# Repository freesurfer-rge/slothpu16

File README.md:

# slothpu16

This is a major revision of [an earlier project](http://www.github.com/freesurfer-rge/slothpu/) to build a computer from 7400-series logic.
This implements a simple 16-bit CPU with a load/store architecture.

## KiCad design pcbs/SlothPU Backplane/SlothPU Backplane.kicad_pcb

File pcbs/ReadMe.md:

# SlothPU16 PCBs

This directory contains the KiCAD files which constitute SlothPU16.
They do rely on [my KiCAD components library](https://github.com/freesurfer-rge/kicad-components), and [one board](https://github.com/freesurfer-rge/slothpu/tree/main/pcbs/Tester) from the original SlothPU.

## General Description

SlothPU16 consists of five modules connected via a backplane:

- The Arithmetic Logic Unit (ALU)
- The Register File
- The Instruction Register
- The Program Counter
- The Pi Backplane Connector

The modules connect to the backplane (and backplane units connect to each other) with a common bus made from two 2x20 pin headers.
With the exception of the Pi Backplane Connector, each of these modules consists of a *carrier* board, which accepts daughter boards via 44-contact edge connectors.
For testing the daughter boards, *connector* PCBs are provided, which allow each to be tested via the [tester board from the original SlothPU](https://github.com/freesurfer-rge/slothpu/tree/main/pcbs/Tester).
While these connector boards also have twin 2x20 pin headers, these **do not** correspond to the Common Bus, and can **only** be used with the Tester board.
The carrier boards which constitute an entire functional module can also be tested in isolation by use of the Pi Backplane connector.

## The Common Bus

The common bus consists of two 2x20 pin headers, offering a total of 80 potential connections.
Not all of the pins are used, but the bus carries:

- The 16-bit A, B and C operand buses
- The 16-bit instruction bus
- Clock and Reset lines
- Signal lines for the individual clock cycles (Instruction Read, Instruction Store, Decode/Execute, Commit, PC Update)

## The Arithmetic Logic Unit

The ALU consists of its [carrier board](./ALU%20Carrier/) and the following daughter cards:

- [Barrel shifter](./Barrel%20Shifter/)
- [NAND/XOR](./NAND%20XOR/)
- [Comparator](./Comparator/)
- [Adder/Subtractor](./Adder%20Subtractor/)

With the exception of the comparator, two of each of these cards are required.
For testing purposes, the barrel shifter has its [own connector](./Barrel%20Shifter%20Connector/), while the other three share a [common connector](./ALU%20Test%20Connector/).
Note that *only one* of the daughter cards should plugged into the common ALU test connector at a time - no effort is made to prevent outputs from different daughter cards being connected.
Remember that **neither connector** uses the common bus.

## The Register File

The [Register File Carrier](./Register%20File%20Carrier/) accepts four identical copies of the [Register File](./Register%20File/).
Each Register file contains eight 8-bit registers, with one write port (from the C bus) and two read ports (the A & B buses).
A [connector](./Register%20File%20Connector/) allows the individual Register Files to be tested (remember that the connector board does **not** use the common bus).

## The Instruction Register

The [Instruction Register](./Instruction%20Register/) accepts a single daughter card, the 16-bit [Register with Reset](./Register%20with%20Reset/).
In addition to containing the instruction register itself, this module implements the 'SET' instruction.
This Register is supposed to be set to zero when power is connected, but for some reason it doesn't.
However, the Reset line does work correctly.
A [connector](./RwR%20Connector/) is provided for testing the register itself (remember that the connector board does **not** use the common bus).

## Program Counter

The [Program Counter](./Program%20Counter/) has two daughter cards - a second Register With Reset (which is the PC register) and an [incrementer](./Incrementer/).
The latter takes care of incrementing the program counter by two (unless a branch is taken), and has its own [test connector board](./Incrementer%20Connector/) (remember that the connector board does **not** use the common bus).

## Pi Backplane Connector

As the name suggests, [this board](./SlothPU%20Backplane/) connects a the standard 2x20 Raspberry Pi header to the Common Bus.
To this end, twin banks of input and output shift registers are used.
The output shift registers can have their outputs set to high impedance for when a connected module wishes to write to a bus.
However, the resolution of this impedance switch is at the bus level, not individual lines.

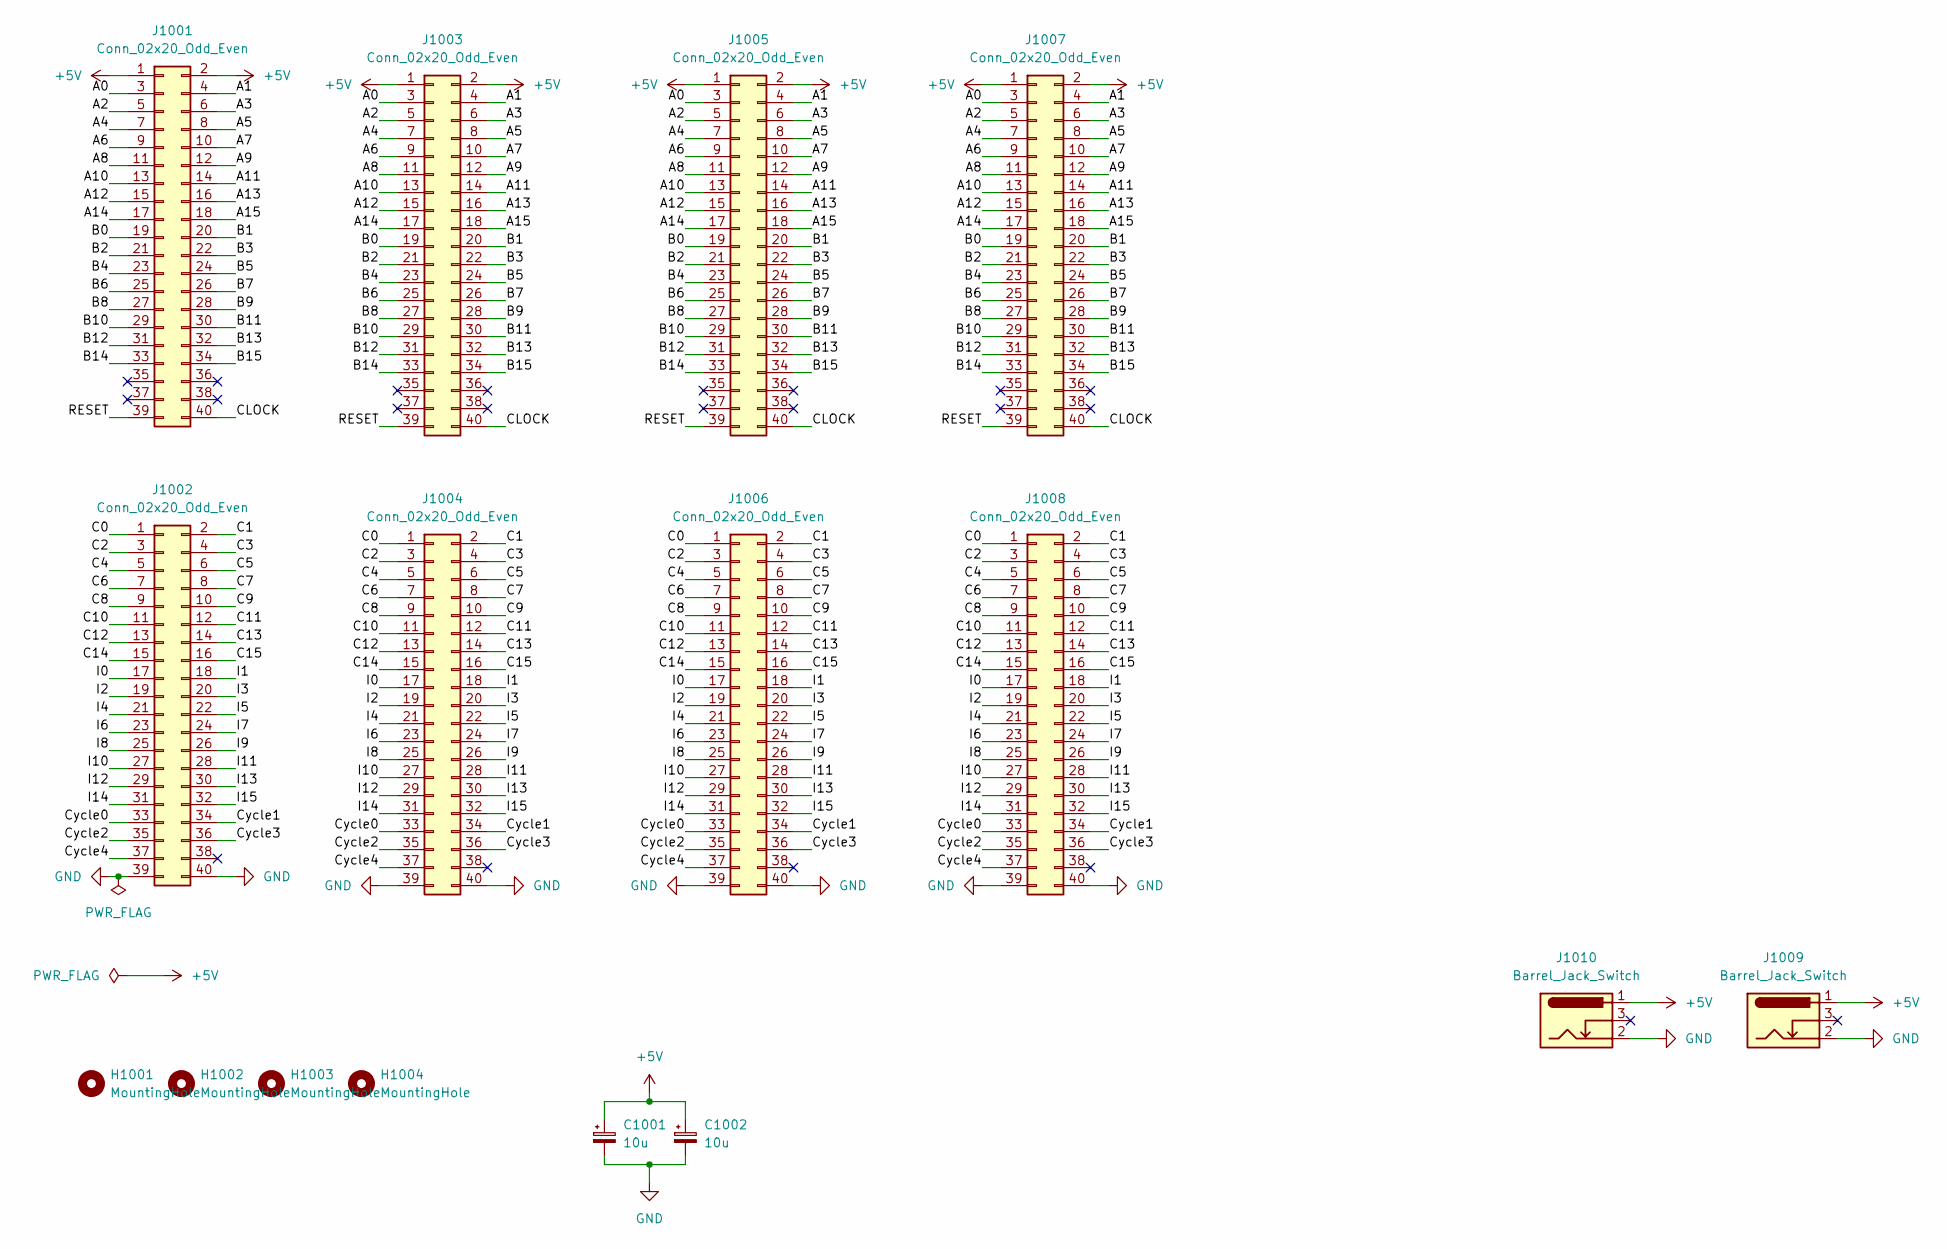
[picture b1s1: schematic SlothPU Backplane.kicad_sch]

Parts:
C1001, C1002: 10u; CP_Radial_D4.0mm_P1.50mm
H1001, H1002, H1003, H1004: MountingHole; MountingHole_2.7mm_M2.5_ISO7380
J1001, J1002, J1003, J1004, J1005, J1006, J1007, J1008: Conn_02x20_Odd_Even; PinHeader_2x20_P2.54mm_Vertical
J1009, J1010: Barrel_Jack_Switch; BarrelJack_Horizontal

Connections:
+5V: C1001.1, C1002.1, J1001.1, J1001.2, J1003.1, J1003.2, J1005.1, J1005.2, J1007.1, J1007.2, J1009.1, J1010.1
/A0: J1001.3, J1003.3, J1005.3, J1007.3
/A1: J1001.4, J1003.4, J1005.4, J1007.4
/A2: J1001.5, J1003.5, J1005.5, J1007.5
/A3: J1001.6, J1003.6, J1005.6, J1007.6
/A4: J1001.7, J1003.7, J1005.7, J1007.7
/A5: J1001.8, J1003.8, J1005.8, J1007.8
/A6: J1001.9, J1003.9, J1005.9, J1007.9
/A7: J1001.10, J1003.10, J1005.10, J1007.10
/A8: J1001.11, J1003.11, J1005.11, J1007.11
/A9: J1001.12, J1003.12, J1005.12, J1007.12
/A10: J1001.13, J1003.13, J1005.13, J1007.13
/A11: J1001.14, J1003.14, J1005.14, J1007.14
/A12: J1001.15, J1003.15, J1005.15, J1007.15
/A13: J1001.16, J1003.16, J1005.16, J1007.16
/A14: J1001.17, J1003.17, J1005.17, J1007.17
/A15: J1001.18, J1003.18, J1005.18, J1007.18
/B0: J1001.19, J1003.19, J1005.19, J1007.19
/B1: J1001.20, J1003.20, J1005.20, J1007.20
/B2: J1001.21, J1003.21, J1005.21, J1007.21
/B3: J1001.22, J1003.22, J1005.22, J1007.22
/B4: J1001.23, J1003.23, J1005.23, J1007.23
/B5: J1001.24, J1003.24, J1005.24, J1007.24
/B6: J1001.25, J1003.25, J1005.25, J1007.25
/B7: J1001.26, J1003.26, J1005.26, J1007.26
/B8: J1001.27, J1003.27, J1005.27, J1007.27
/B9: J1001.28, J1003.28, J1005.28, J1007.28
/B10: J1001.29, J1003.29, J1005.29, J1007.29
/B11: J1001.30, J1003.30, J1005.30, J1007.30
/B12: J1001.31, J1003.31, J1005.31, J1007.31
/B13: J1001.32, J1003.32, J1005.32, J1007.32
/B14: J1001.33, J1003.33, J1005.33, J1007.33
/B15: J1001.34, J1003.34, J1005.34, J1007.34
/C0: J1002.1, J1004.1, J1006.1, J1008.1
/C1: J1002.2, J1004.2, J1006.2, J1008.2
/C2: J1002.3, J1004.3, J1006.3, J1008.3
/C3: J1002.4, J1004.4, J1006.4, J1008.4
/C4: J1002.5, J1004.5, J1006.5, J1008.5
/C5: J1002.6, J1004.6, J1006.6, J1008.6
/C6: J1002.7, J1004.7, J1006.7, J1008.7
/C7: J1002.8, J1004.8, J1006.8, J1008.8
/C8: J1002.9, J1004.9, J1006.9, J1008.9
/C9: J1002.10, J1004.10, J1006.10, J1008.10
/C10: J1002.11, J1004.11, J1006.11, J1008.11
/C11: J1002.12, J1004.12, J1006.12, J1008.12
/C12: J1002.13, J1004.13, J1006.13, J1008.13
/C13: J1002.14, J1004.14, J1006.14, J1008.14
/C14: J1002.15, J1004.15, J1006.15, J1008.15
/C15: J1002.16, J1004.16, J1006.16, J1008.16
/CLOCK: J1001.40, J1003.40, J1005.40, J1007.40
/Cycle0: J1002.33, J1004.33, J1006.33, J1008.33
/Cycle1: J1002.34, J1004.34, J1006.34, J1008.34
/Cycle2: J1002.35, J1004.35, J1006.35, J1008.35
/Cycle3: J1002.36, J1004.36, J1006.36, J1008.36
/Cycle4: J1002.37, J1004.37, J1006.37, J1008.37
/I0: J1002.17, J1004.17, J1006.17, J1008.17
/I1: J1002.18, J1004.18, J1006.18, J1008.18
/I2: J1002.19, J1004.19, J1006.19, J1008.19
/I3: J1002.20, J1004.20, J1006.20, J1008.20
/I4: J1002.21, J1004.21, J1006.21, J1008.21
/I5: J1002.22, J1004.22, J1006.22, J1008.22
/I6: J1002.23, J1004.23, J1006.23, J1008.23
/I7: J1002.24, J1004.24, J1006.24, J1008.24
/I8: J1002.25, J1004.25, J1006.25, J1008.25
/I9: J1002.26, J1004.26, J1006.26, J1008.26
/I10: J1002.27, J1004.27, J1006.27, J1008.27
/I11: J1002.28, J1004.28, J1006.28, J1008.28
/I12: J1002.29, J1004.29, J1006.29, J1008.29
/I13: J1002.30, J1004.30, J1006.30, J1008.30
/I14: J1002.31, J1004.31, J1006.31, J1008.31
/I15: J1002.32, J1004.32, J1006.32, J1008.32
/RESET: J1001.39, J1003.39, J1005.39, J1007.39
GND: C1001.2, C1002.2, J1002.39, J1002.40, J1004.39, J1004.40, J1006.39, J1006.40, J1008.39, J1008.40, J1009.2, J1010.2

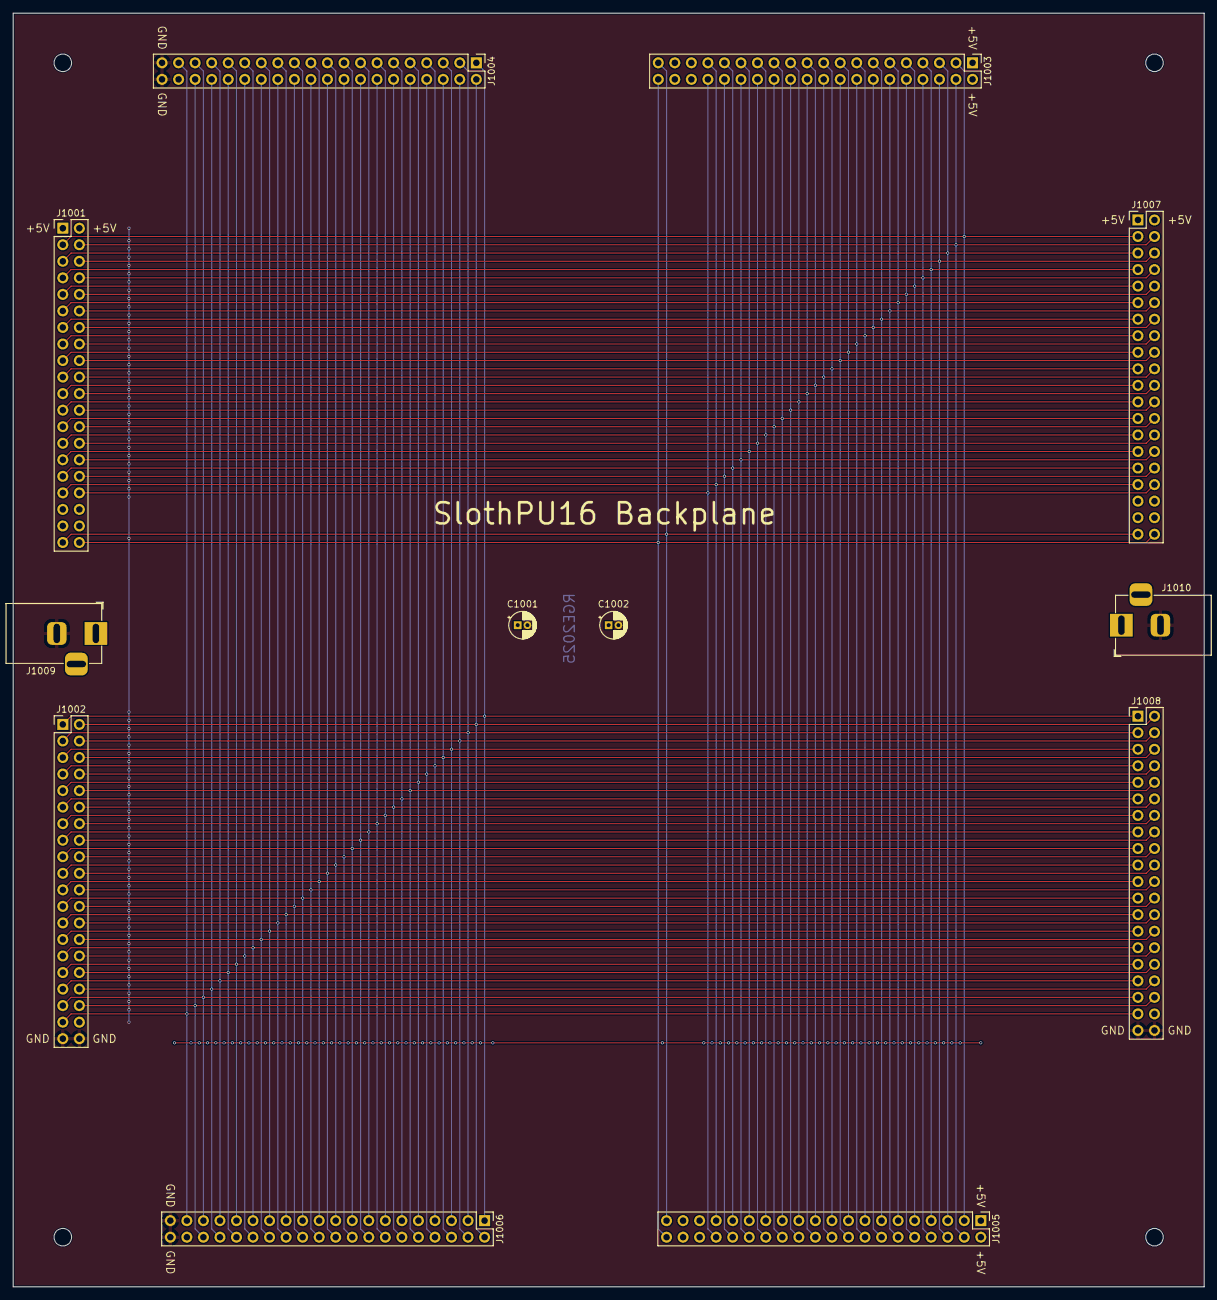
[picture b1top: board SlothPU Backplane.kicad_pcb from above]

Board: 2 copper layers, 182.9 x 195.6 mm, 16 parts (0 on the bottom side), 73 nets.

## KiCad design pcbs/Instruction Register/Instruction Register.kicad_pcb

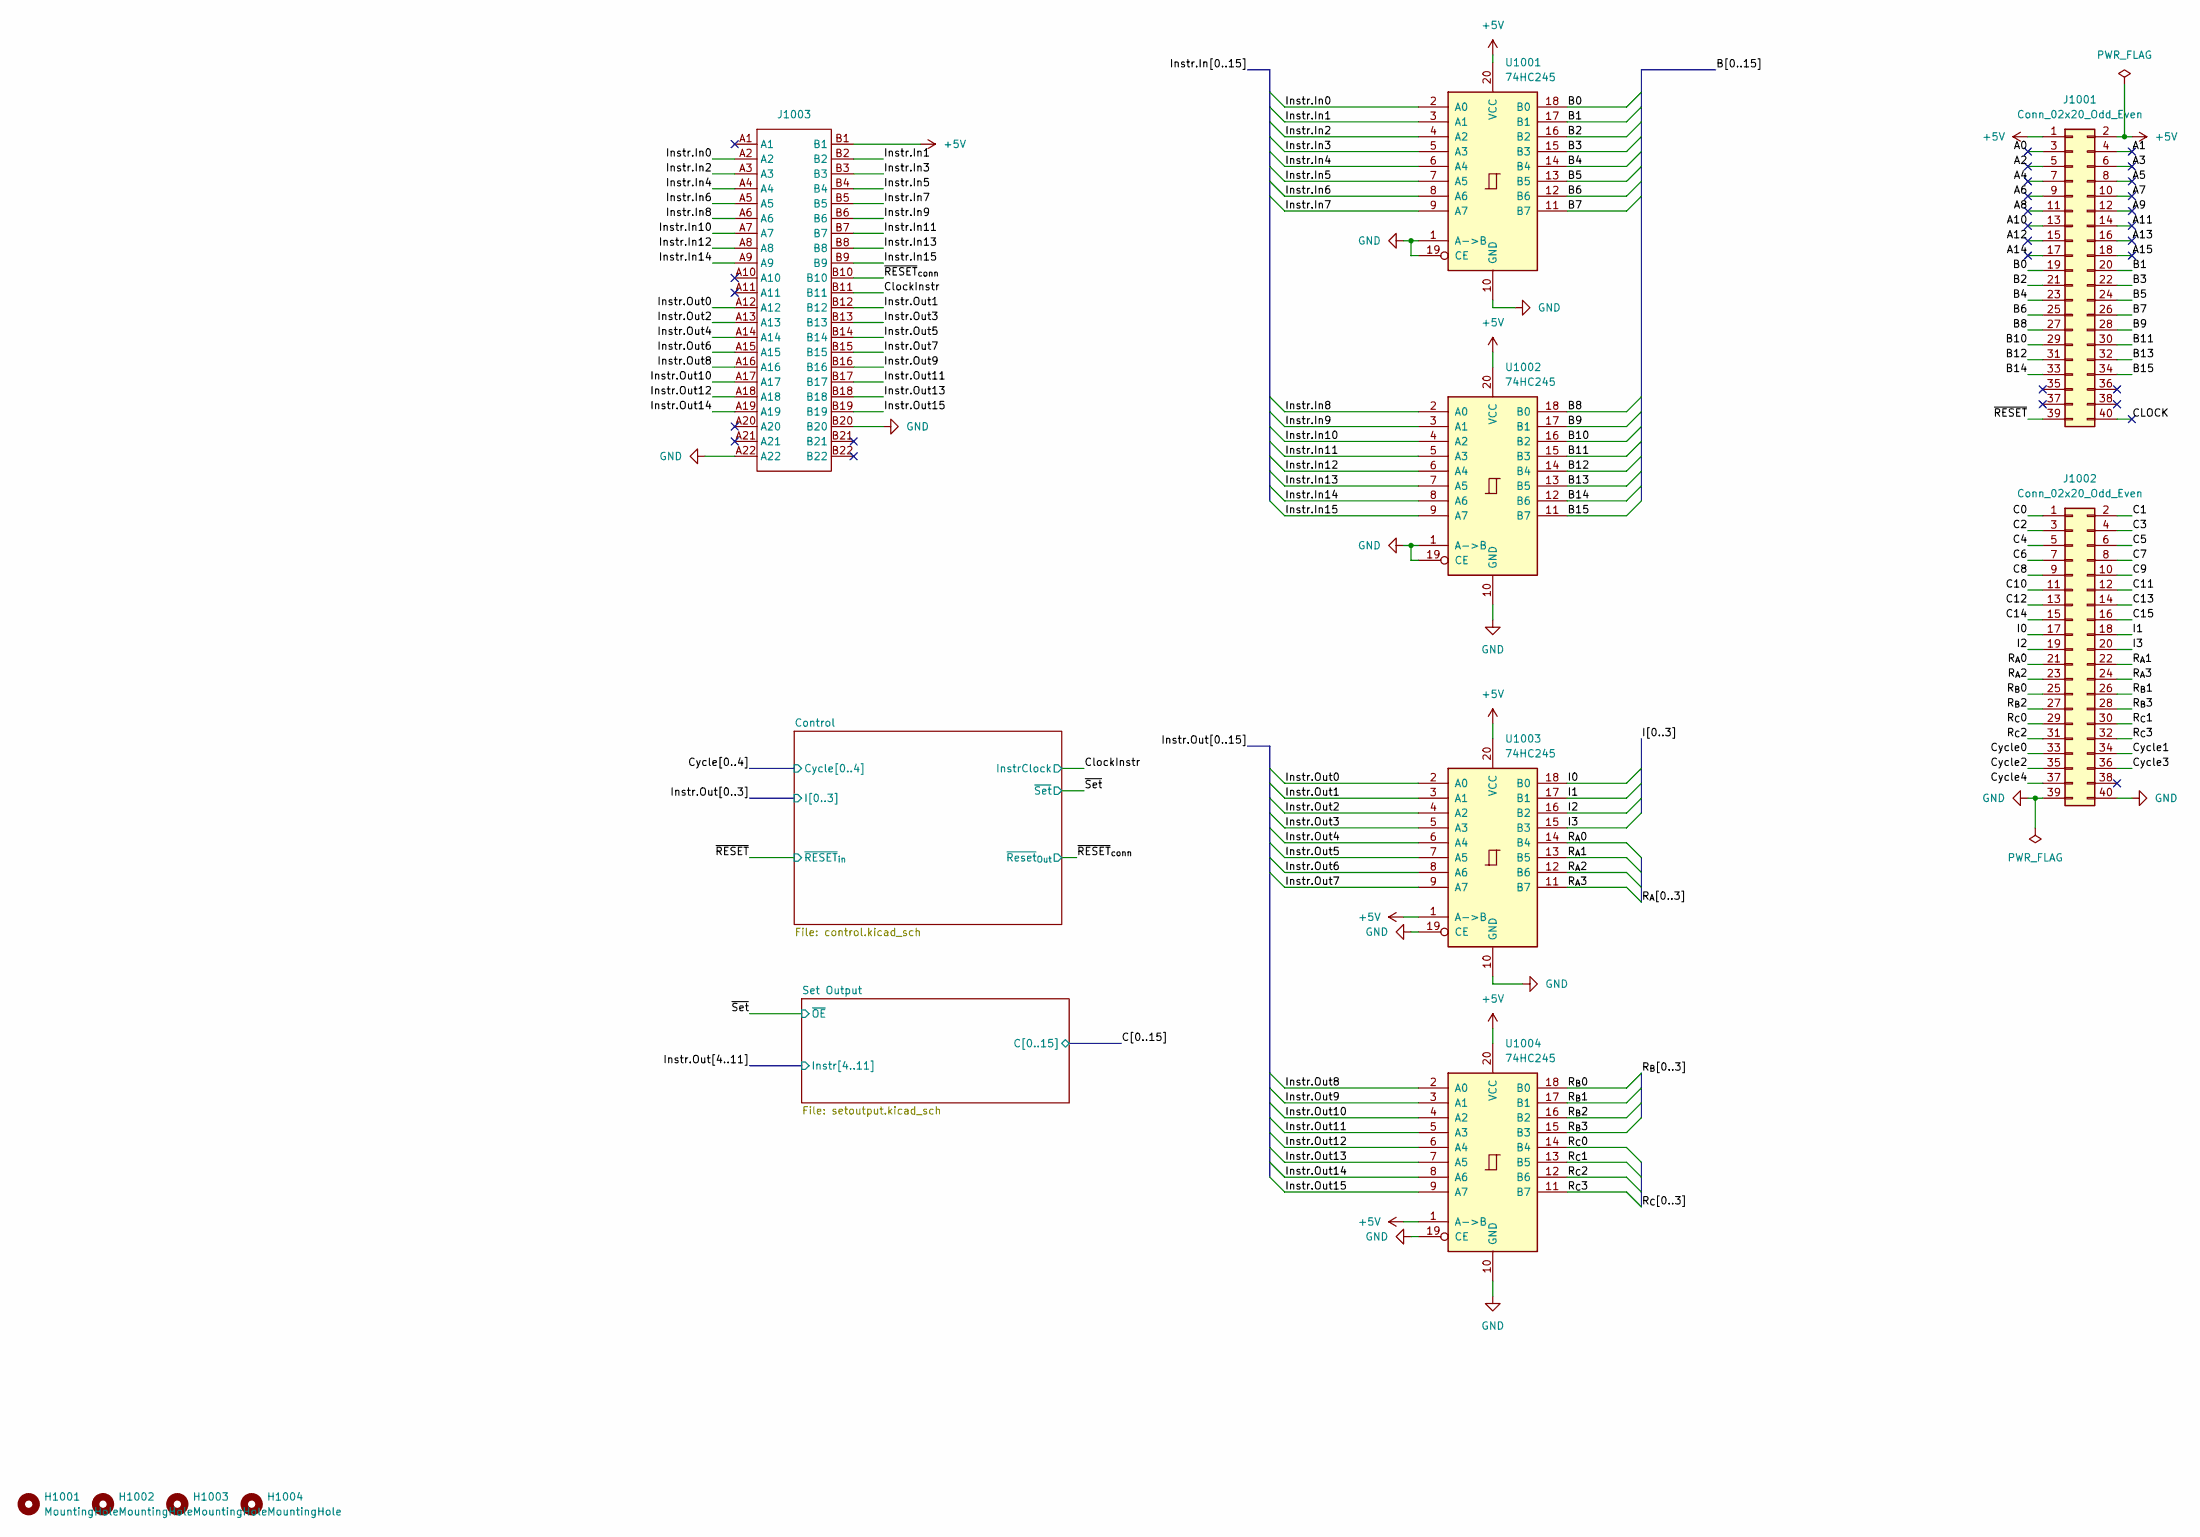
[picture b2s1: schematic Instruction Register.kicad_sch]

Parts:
H1001, H1002, H1003, H1004: MountingHole; MountingHole_2.7mm_M2.5_ISO7380
J1001, J1002: Conn_02x20_Odd_Even; PinHeader_2x20_P2.54mm_Vertical
J1003: TE-5530843-4-Mount
U1001, U1002, U1003, U1004: 74HC245; SOIC-20W_7.5x12.8mm_P1.27mm; LCSC C5625

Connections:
+5V: J1001.1, J1001.2, J1003.B1, U1001.20 (VCC), U1002.20 (VCC), U1003.1 (A->B), U1003.20 (VCC), U1004.1 (A->B), U1004.20 (VCC); also elsewhere on the board
/A0: J1001.3
/A1: J1001.4
/A2: J1001.5
/A3: J1001.6
/A4: J1001.7
/A5: J1001.8
/A6: J1001.9
/A7: J1001.10
/A8: J1001.11
/A9: J1001.12
/A10: J1001.13
/A11: J1001.14
/A12: J1001.15
/A13: J1001.16
/A14: J1001.17
/A15: J1001.18
/B0: J1001.19, U1001.18 (B0)
/B1: J1001.20, U1001.17 (B1)
/B2: J1001.21, U1001.16 (B2)
/B3: J1001.22, U1001.15 (B3)
/B4: J1001.23, U1001.14 (B4)
/B5: J1001.24, U1001.13 (B5)
/B6: J1001.25, U1001.12 (B6)
/B7: J1001.26, U1001.11 (B7)
/B8: J1001.27, U1002.18 (B0)
/B9: J1001.28, U1002.17 (B1)
/B10: J1001.29, U1002.16 (B2)
/B11: J1001.30, U1002.15 (B3)
/B12: J1001.31, U1002.14 (B4)
/B13: J1001.32, U1002.13 (B5)
/B14: J1001.33, U1002.12 (B6)
/B15: J1001.34, U1002.11 (B7)
/C0: J1002.1; also elsewhere on the board
/C1: J1002.2; also elsewhere on the board
/C2: J1002.3; also elsewhere on the board
/C3: J1002.4; also elsewhere on the board
/C4: J1002.5; also elsewhere on the board
/C5: J1002.6; also elsewhere on the board
/C6: J1002.7; also elsewhere on the board
/C7: J1002.8; also elsewhere on the board
/C8: J1002.9; also elsewhere on the board
/C9: J1002.10; also elsewhere on the board
/C10: J1002.11; also elsewhere on the board
/C11: J1002.12; also elsewhere on the board
/C12: J1002.13; also elsewhere on the board
/C13: J1002.14; also elsewhere on the board
/C14: J1002.15; also elsewhere on the board
/C15: J1002.16; also elsewhere on the board
/CLOCK: J1001.40
/ClockInstr: J1003.B11; also elsewhere on the board
/Cycle0: J1002.33
/Cycle1: J1002.34; also elsewhere on the board
/Cycle2: J1002.35; also elsewhere on the board
/Cycle3: J1002.36; also elsewhere on the board
/Cycle4: J1002.37; also elsewhere on the board
/I0: J1002.17, U1003.18 (B0)
/I1: J1002.18, U1003.17 (B1)
/I2: J1002.19, U1003.16 (B2)
/I3: J1002.20, U1003.15 (B3)
/Instr.In0: J1003.A2, U1001.2 (A0)
/Instr.In1: J1003.B2, U1001.3 (A1)
/Instr.In2: J1003.A3, U1001.4 (A2)
/Instr.In3: J1003.B3, U1001.5 (A3)
/Instr.In4: J1003.A4, U1001.6 (A4)
/Instr.In5: J1003.B4, U1001.7 (A5)
/Instr.In6: J1003.A5, U1001.8 (A6)
/Instr.In7: J1003.B5, U1001.9 (A7)
/Instr.In8: J1003.A6, U1002.2 (A0)
/Instr.In9: J1003.B6, U1002.3 (A1)
/Instr.In10: J1003.A7, U1002.4 (A2)
/Instr.In11: J1003.B7, U1002.5 (A3)
/Instr.In12: J1003.A8, U1002.6 (A4)
/Instr.In13: J1003.B8, U1002.7 (A5)
/Instr.In14: J1003.A9, U1002.8 (A6)
/Instr.In15: J1003.B9, U1002.9 (A7)
/Instr.Out0: J1003.A12, U1003.2 (A0); also elsewhere on the board
/Instr.Out1: J1003.B12, U1003.3 (A1); also elsewhere on the board
/Instr.Out2: J1003.A13, U1003.4 (A2); also elsewhere on the board
/Instr.Out3: J1003.B13, U1003.5 (A3); also elsewhere on the board
/Instr.Out4: J1003.A14, U1003.6 (A4); also elsewhere on the board
/Instr.Out5: J1003.B14, U1003.7 (A5); also elsewhere on the board
/Instr.Out6: J1003.A15, U1003.8 (A6); also elsewhere on the board
/Instr.Out7: J1003.B15, U1003.9 (A7); also elsewhere on the board
/Instr.Out8: J1003.A16, U1004.2 (A0); also elsewhere on the board
/Instr.Out9: J1003.B16, U1004.3 (A1); also elsewhere on the board
/Instr.Out10: J1003.A17, U1004.4 (A2); also elsewhere on the board
/Instr.Out11: J1003.B17, U1004.5 (A3); also elsewhere on the board
/Instr.Out12: J1003.A18, U1004.6 (A4)
/Instr.Out13: J1003.B18, U1004.7 (A5)
/Instr.Out14: J1003.A19, U1004.8 (A6)
/Instr.Out15: J1003.B19, U1004.9 (A7)
/R_{A}0: J1002.21, U1003.14 (B4)
/R_{A}1: J1002.22, U1003.13 (B5)
/R_{A}2: J1002.23, U1003.12 (B6)
/R_{A}3: J1002.24, U1003.11 (B7)
/R_{B}0: J1002.25, U1004.18 (B0)
/R_{B}1: J1002.26, U1004.17 (B1)
/R_{B}2: J1002.27, U1004.16 (B2)
/R_{B}3: J1002.28, U1004.15 (B3)
/R_{C}0: J1002.29, U1004.14 (B4)
/R_{C}1: J1002.30, U1004.13 (B5)
/R_{C}2: J1002.31, U1004.12 (B6)
/R_{C}3: J1002.32, U1004.11 (B7)
/~RESET: J1001.39; also elsewhere on the board
/~RESET_{conn}: J1003.B10; also elsewhere on the board
GND: J1002.39, J1002.40, J1003.A22, J1003.B20, U1001.1 (A->B), U1001.10 (GND), U1001.19 (CE), U1002.1 (A->B), U1002.10 (GND), U1002.19 (CE), U1003.10 (GND), U1003.19 (CE), U1004.10 (GND), U1004.19 (CE); also elsewhere on the board

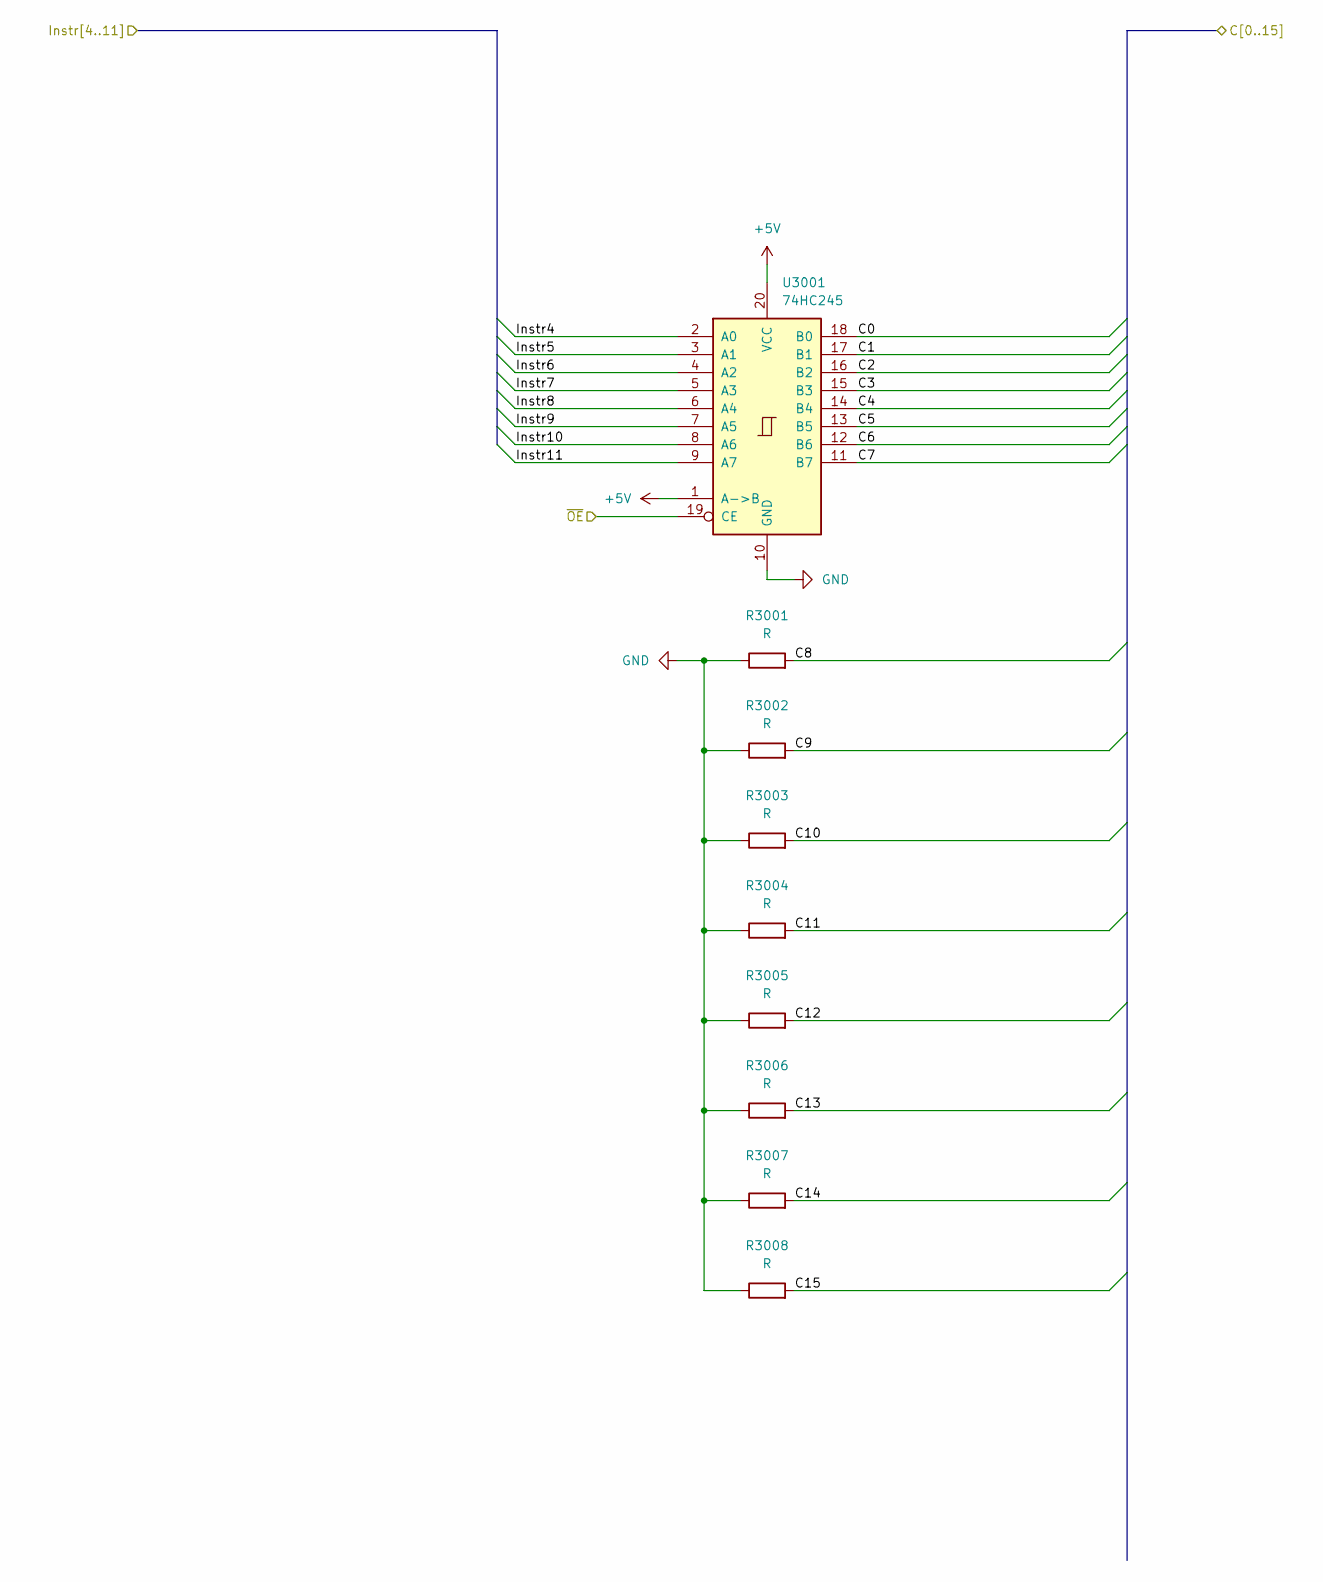
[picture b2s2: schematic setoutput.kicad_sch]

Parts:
R3001, R3002, R3003, R3004, R3005, R3006, R3007, R3008: R; R_0603_1608Metric; LCSC C22935
U3001: 74HC245; SOIC-20W_7.5x12.8mm_P1.27mm; LCSC C5625

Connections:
+5V: U3001.1 (A->B), U3001.20 (VCC); also elsewhere on the board
/C0: U3001.18 (B0); also elsewhere on the board
/C1: U3001.17 (B1); also elsewhere on the board
/C2: U3001.16 (B2); also elsewhere on the board
/C3: U3001.15 (B3); also elsewhere on the board
/C4: U3001.14 (B4); also elsewhere on the board
/C5: U3001.13 (B5); also elsewhere on the board
/C6: U3001.12 (B6); also elsewhere on the board
/C7: U3001.11 (B7); also elsewhere on the board
/C8: R3001.2; also elsewhere on the board
/C9: R3002.2; also elsewhere on the board
/C10: R3003.2; also elsewhere on the board
/C11: R3004.2; also elsewhere on the board
/C12: R3005.2; also elsewhere on the board
/C13: R3006.2; also elsewhere on the board
/C14: R3007.2; also elsewhere on the board
/C15: R3008.2; also elsewhere on the board
/Instr.Out4: U3001.2 (A0); also elsewhere on the board
/Instr.Out5: U3001.3 (A1); also elsewhere on the board
/Instr.Out6: U3001.4 (A2); also elsewhere on the board
/Instr.Out7: U3001.5 (A3); also elsewhere on the board
/Instr.Out8: U3001.6 (A4); also elsewhere on the board
/Instr.Out9: U3001.7 (A5); also elsewhere on the board
/Instr.Out10: U3001.8 (A6); also elsewhere on the board
/Instr.Out11: U3001.9 (A7); also elsewhere on the board
/~Set: U3001.19 (CE); also elsewhere on the board
GND: R3001.1, R3002.1, R3003.1, R3004.1, R3005.1, R3006.1, R3007.1, R3008.1, U3001.10 (GND); also elsewhere on the board

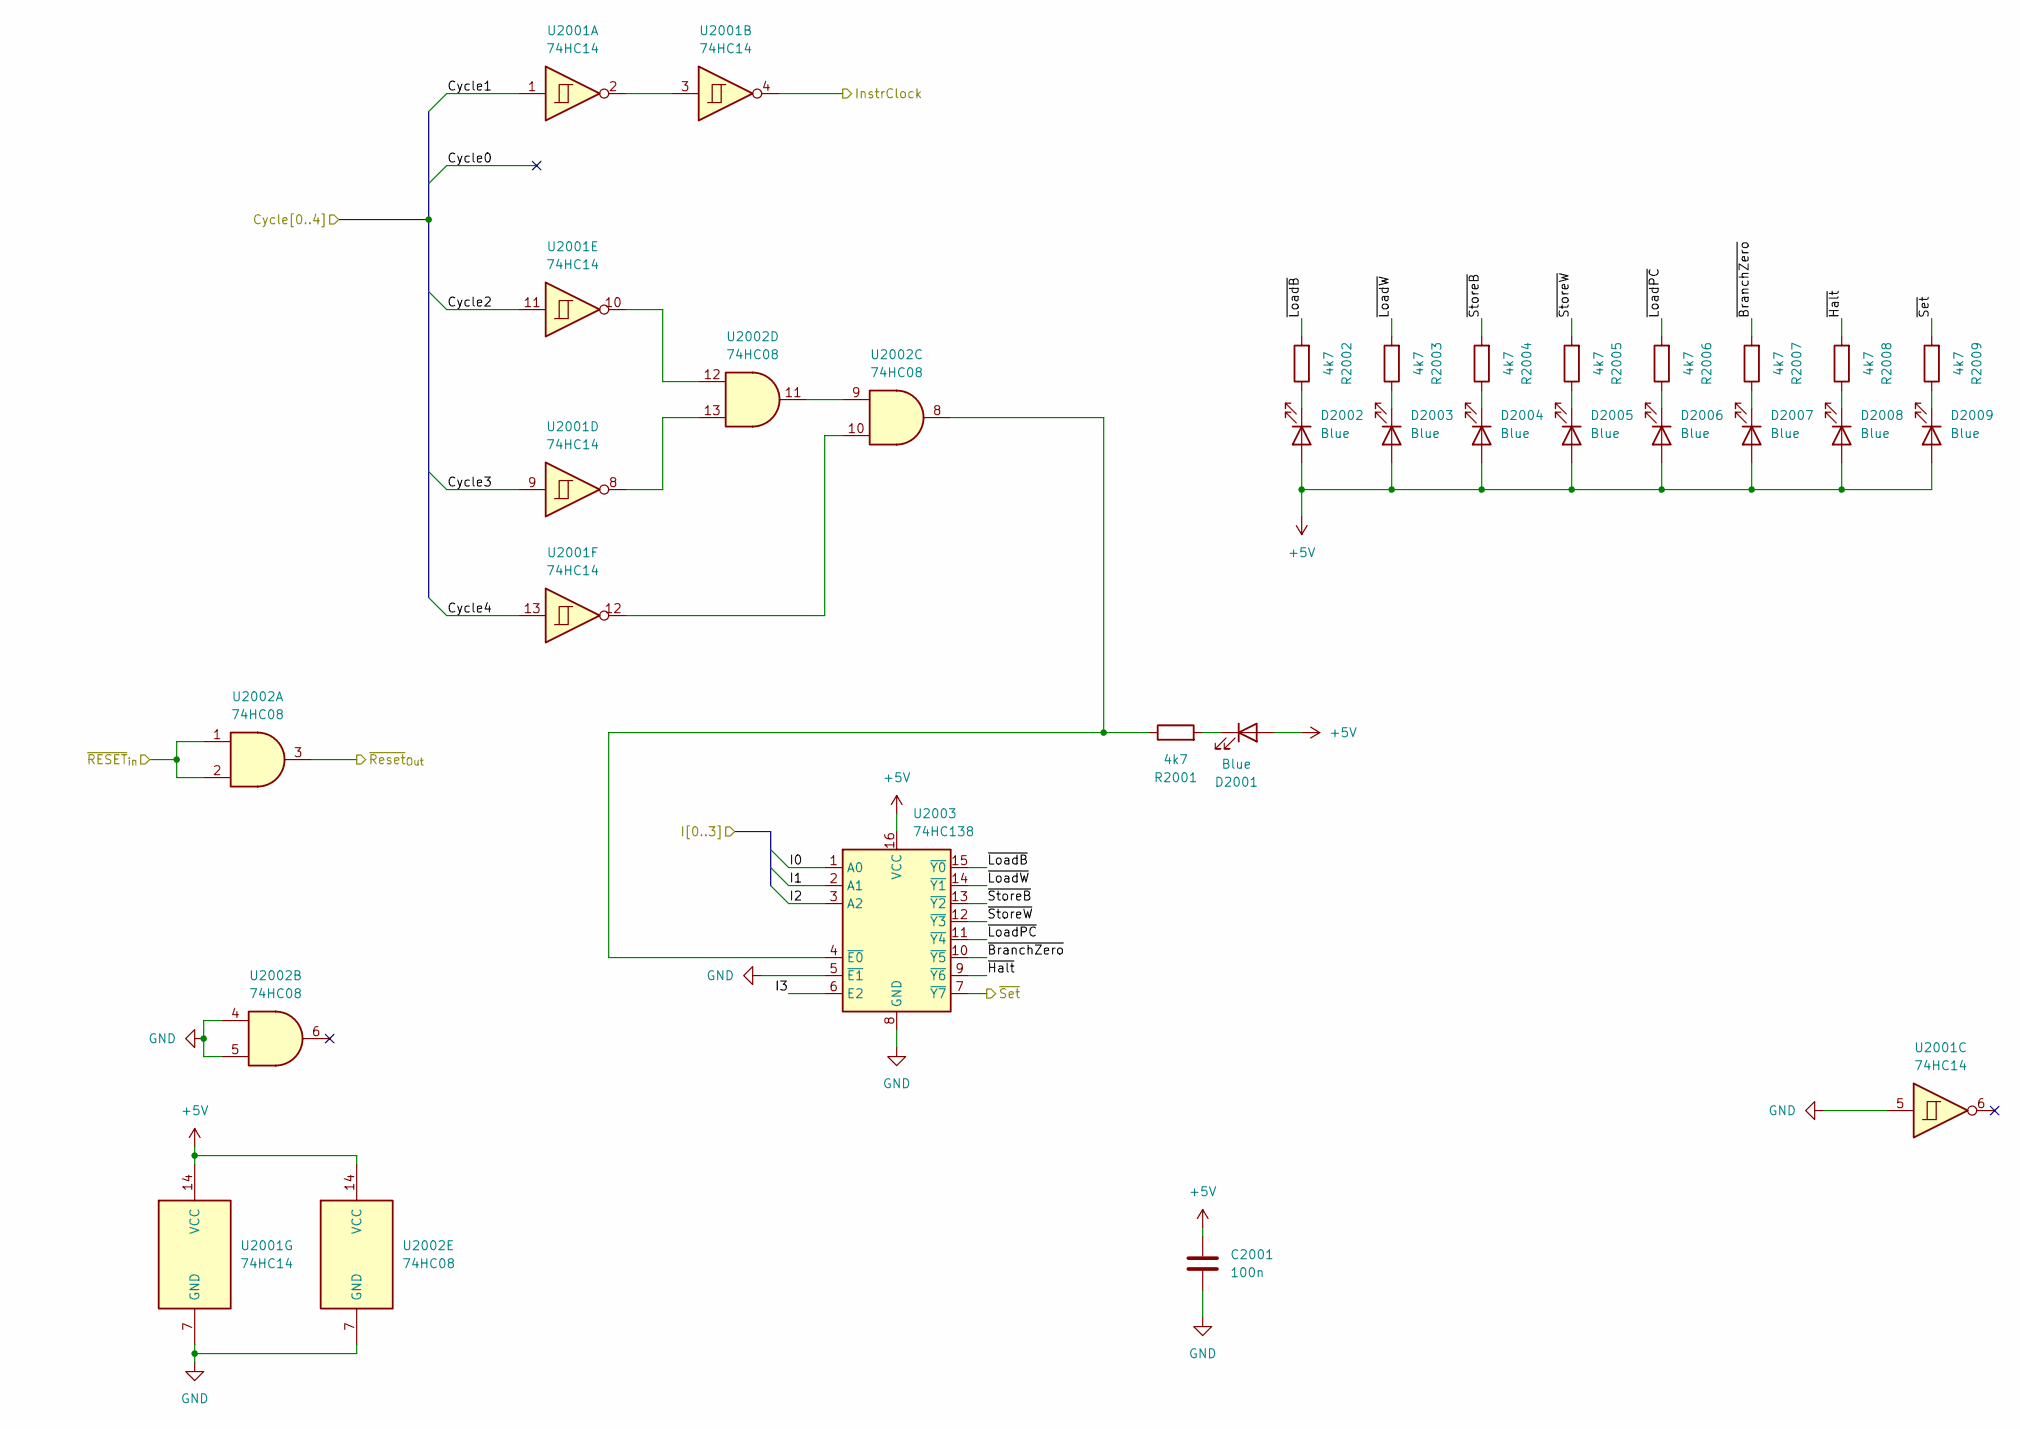
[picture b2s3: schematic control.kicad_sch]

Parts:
C2001: 100n; C_0603_1608Metric; LCSC C14663
D2001, D2002, D2003, D2004, D2005, D2006, D2007, D2008, D2009: Blue; LED_0603_1608Metric; LCSC C72041
R2001, R2002, R2003, R2004, R2005, R2006, R2007, R2008, R2009: 4k7; R_0603_1608Metric; LCSC C23162
U2001: 74HC14; SOIC-14_3.9x8.7mm_P1.27mm; LCSC C5605
U2002: 74HC08; SOIC-14_3.9x8.7mm_P1.27mm; LCSC C5593
U2003: 74HC138; DIP-16_W7.62mm_Socket

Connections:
+5V: C2001.1, D2001.2 (A), D2002.2 (A), D2003.2 (A), D2004.2 (A), D2005.2 (A), D2006.2 (A), D2007.2 (A), D2008.2 (A), D2009.2 (A), U2001.14 (VCC), U2002.14 (VCC), U2003.16 (VCC); also elsewhere on the board
/ClockInstr: U2001.4; also elsewhere on the board
/Control/~BranchZero: R2007.2, U2003.10 (~Y5)
/Control/~Halt: R2008.2, U2003.9 (~Y6)
/Control/~LoadB: R2002.2, U2003.15 (~Y0)
/Control/~LoadPC: R2006.2, U2003.11 (~Y4)
/Control/~LoadW: R2003.2, U2003.14 (~Y1)
/Control/~StoreB: R2004.2, U2003.13 (~Y2)
/Control/~StoreW: R2005.2, U2003.12 (~Y3)
/Cycle1: U2001.1; also elsewhere on the board
/Cycle2: U2001.11; also elsewhere on the board
/Cycle3: U2001.9; also elsewhere on the board
/Cycle4: U2001.13; also elsewhere on the board
/Instr.Out0: U2003.1 (A0); also elsewhere on the board
/Instr.Out1: U2003.2 (A1); also elsewhere on the board
/Instr.Out2: U2003.3 (A2); also elsewhere on the board
/Instr.Out3: U2003.6 (E2); also elsewhere on the board
/~RESET: U2002.1, U2002.2; also elsewhere on the board
/~RESET_{conn}: U2002.3; also elsewhere on the board
/~Set: R2009.2, U2003.7 (~Y7); also elsewhere on the board
GND: C2001.2, U2001.5, U2001.7 (GND), U2002.4, U2002.5, U2002.7 (GND), U2003.5 (~E1), U2003.8 (GND); also elsewhere on the board
unnamed: D2001.1 (K), R2001.2
unnamed: D2002.1 (K), R2002.1
unnamed: D2003.1 (K), R2003.1
unnamed: D2004.1 (K), R2004.1
unnamed: D2005.1 (K), R2005.1
unnamed: D2006.1 (K), R2006.1
unnamed: D2007.1 (K), R2007.1
unnamed: D2008.1 (K), R2008.1
unnamed: D2009.1 (K), R2009.1
unnamed: U2001.2, U2001.3
unnamed: U2001.8, U2002.13
unnamed: U2001.10, U2002.12
unnamed: U2001.12, U2002.10
unnamed: U2002.9, U2002.11
unnamed: R2001.1, U2002.8, U2003.4 (~E0)

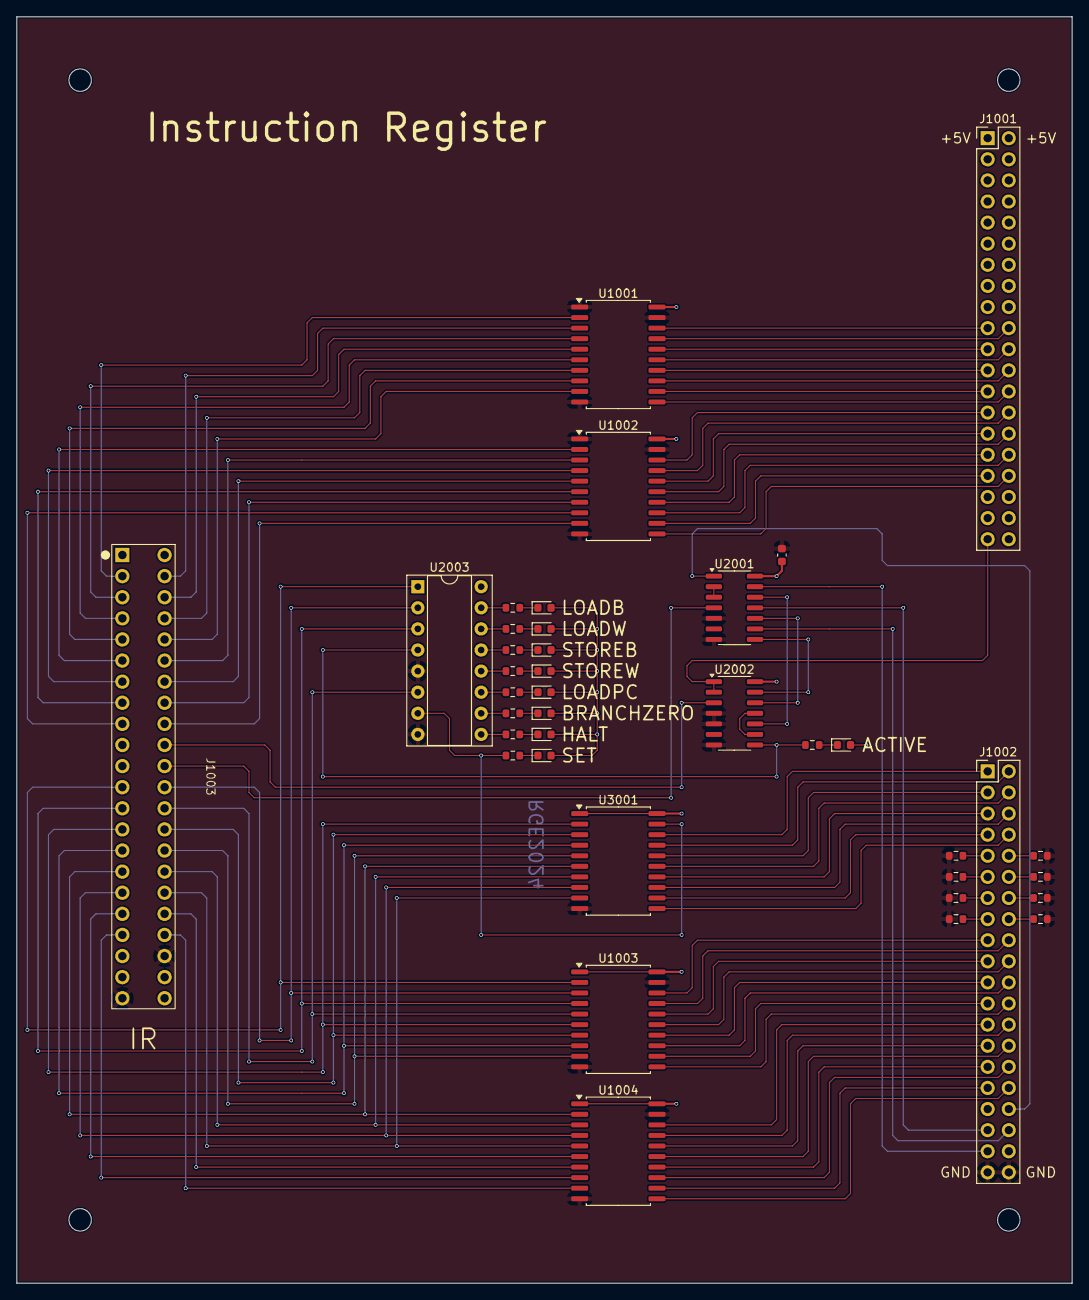
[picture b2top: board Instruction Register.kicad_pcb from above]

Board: 2 copper layers, 127.0 x 152.4 mm, 42 parts (0 on the bottom side), 112 nets.
